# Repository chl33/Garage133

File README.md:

# Garage133

**Garage133** is a DIY garage door automation and monitoring system based on the ESP32 / ESP32-S3.
It provides the capability to remotely control up to two garage doors, monitor their
 state (open/closed), detect vehicle presence using a multi-sonar sensor array,
 measure environmental conditions (temperature/humidity), and detect motion within the garage.

The system integrates seamlessly with **Home Assistant** via MQTT Discovery
 and provides a modern, responsive **Svelte-based Web Interface** for real-time monitoring
 and configuration.

## What's New in v2.1.0

*   **Board v3.1 PCB & Enclosure Updates**: Updated KiCAD design for board v3.1, refined BOM, and enhanced 3D-printed enclosure with labeled connectors, improved USB-C port clearance, and better thermal isolation for the SHTC3 sensor.
*   **Standardized on ESP32-S3 (Board v3.x)**: Retired support and pin definitions for legacy Classic ESP32 (Board v1/v2).
*   **Sonar Watchdog & Stability**: Added sonar ping timeout handling to prevent missed echoes from triggering the ESP32 hardware watchdog.
*   **HMM Visualization & Retraining Tools**: Added an SVG state diagram visualization tool (`analysis/hmm_to_svg.py`) and streamlined characterization workflow in `analysis/retrain.py`.
*   **Published Library Dependencies**: Switched dependency management to published packages (`chl33/og3@^0.7.0`, `chl33/og3x-oled@^0.6.1`, `chl33/og3x-shtc3@^0.6.0`).

## What's New in v2.0.0

*   **Quad-Sonar Array (Dual Sonars per Bay)**: Upgraded from single to dual HC-SR04 ultrasonic sensors per garage door (4 sonars total), providing substantially more robust vehicle detection and door state estimation.
*   **Hardware Board v3.0 (ESP32-S3 Support)**: Added support for the v3.0 PCB powered by the ESP32-S3, featuring updated pin routings, 8MB flash support, and refreshed 3D solder stencil fixtures.
*   **Home Assistant Probability Sensors**: Added real-time HMM state probabilities (`probOpen`, `probCar`, `probEmpty`) to Home Assistant via MQTT Discovery.
*   **Hardened Web UI Build Pipeline**: Pinned `svelteesp32` to v3.2.5 and upgraded GitHub Actions workflows to Node 22 for reliable, deterministic builds.

## Features

*   **Dual Door Control:** Independent control for two garage doors using relays.
*   **Quad-Sonar HMM State Estimation:** Uses **Hidden Markov Models (HMM)** and a 4-sonar sensor array to robustly classify states:
    *   **Open** (Door is rolled up).
    *   **Closed with Car** (Door is down, vehicle present in bay).
    *   **Closed (Empty)** (Door is down, bay is empty).
*   **Modern Web Dashboard:** A responsive Svelte Single Page Application (SPA) to:
    *   Monitor real-time sensor data and door status.
    *   Trigger door relays remotely.
    *   Visualize HMM detection probabilities in real time.
    *   Manually correct and label states to refine detection.
    *   Upload and reload HMM JSON models dynamically.
*   **Environmental Monitoring:** SHTC3 sensor for Temperature and Humidity.
*   **Motion & Light Detection:** PIR sensor for motion and analog light sensor for garage illumination levels.
*   **Home Assistant MQTT Discovery:** Automatic entity discovery for covers, binary sensors, environmental gauges, and state probability metrics.
*   **OLED Display:** Shows live status, IP address, and sensor readings locally.
*   **OTA Updates:** Reliable Over-The-Air firmware updates using expanded flash partitions.

## Hardware

Garage133 is designed for the **Board v3.1 / v3.0 (ESP32-S3)**. Earlier Board v1/v2 (Classic ESP32) revisions have been retired.

### Pinout Configuration

| Component | Board v3.1 / v3.0 (ESP32-S3) | Description |
| :--- | :--- | :--- |
| **Relay (Left)** | GPIO 10 | Left Garage Door Relay Command |
| **Relay (Right)** | GPIO 11 | Right Garage Door Relay Command |
| **Sonar 1 Trig / Echo (Left)** | GPIO 1 / GPIO 5 | Primary Left Ultrasonic Sensor |
| **Sonar 2 Trig / Echo (Left)** | GPIO 3 / GPIO 7 | Secondary Left Ultrasonic Sensor |
| **Sonar 1 Trig / Echo (Right)** | GPIO 2 / GPIO 6 | Primary Right Ultrasonic Sensor |
| **Sonar 2 Trig / Echo (Right)** | GPIO 4 / GPIO 15 | Secondary Right Ultrasonic Sensor |
| **PIR Sensor** | GPIO 12 | PIR Motion Detection |
| **Light Sensor** | GPIO 12 | Analog Light Level |
| **I2C SDA / SCL** | GPIO 8 / GPIO 9 | SHTC3 Sensor & OLED Display |

*Note: Pin definitions are configured in [`src/main.cpp`](file:///home/chris/Projects2/Garage133/src/main.cpp).*

### Fabrication

This repository includes files for fabricating the custom PCB and 3D printed case:
*   **KiCAD:** Circuit board schematics and layouts are located in the `KiCAD/` directory.
*   **3D Parts:** OpenSCAD and STL files for the enclosure, sensor mounts, and solder stencil fixtures are in the `scad/` directory.

Sonar sensor mount design is also [published on Printables](https://www.printables.com/model/1741349-sonar-ball-and-socket-mount).

## Getting Started

### Prerequisites
*   [PlatformIO](https://platformio.org/) (VSCode Extension or CLI)
*   [Node.js & npm](https://nodejs.org/) (Node 22+ recommended for building the Web Interface)
*   Git

### Installation & Build

1.  **Clone the repository:**
    ```bash
    git clone https://github.com/chl33/Garage133.git
    cd Garage133
    ```

2.  **Build the Web Interface:**
    Generate the C++ header containing the compiled Svelte SPA:
    ```bash
    ./build-svelte.sh
    ```

3.  **Configuration:**
    Copy the example configuration files and customize your settings:
    ```bash
    cp secrets.ini.example secrets.ini
    cp local.ini.example local.ini
    ```
    *Note: WiFi and MQTT credentials can also be configured via the captive portal on first boot (when connected to the `garage133` AP) or through the web dashboard settings page.*

4.  **Build and Flash:**
    Connect your board via USB for the initial flash:

    *   **USB Flash (ESP32-S3):**
        ```bash
        pio run -e usb_s3 --target upload
        ```
    *   **OTA Updates (once configured on WiFi):**
        ```bash
        pio run -e wifi_s3 --target upload
        ```

## Usage

### Web Interface
Navigate to the device's IP address in your web browser:
*   **Overview:** Real-time status of both garage doors, ultrasonic distances, and environmental readings.
*   **Door Details:** View live HMM probability charts, manually label states to gather training data, or upload new JSON models.
*   **Settings:** Configure WiFi, MQTT broker, and initiate device restarts.

### Home Assistant Integration
The device automatically publishes Home Assistant MQTT Discovery topics:
*   **Covers:** `left_door`, `right_door` (Open/Close control & state feedback)
*   **Sensors:** `temperature`, `humidity`, `light`, `prob_open`, `prob_car`, `prob_empty`
*   **Binary Sensors:** `car` (vehicle presence per bay), `door`, `motion`

### HMM Analysis Toolkit
The `analysis/` directory contains Python tools to train and evaluate multi-sonar classification models:
*   Download historical telemetry logs from Home Assistant or InfluxDB.
*   Train 4-sonar HMM transition and emission models using the Viterbi algorithm.
*   Evaluate accuracy and export optimized JSON models to upload directly via the web UI.

## Blog Post
For background and detailed design notes on this project, check out the [Garage133 Blog Post](https://selectiveappeal.org/posts/garage133/).

## License
This project is licensed under the MIT License - see the [LICENSE](LICENSE) file for details.

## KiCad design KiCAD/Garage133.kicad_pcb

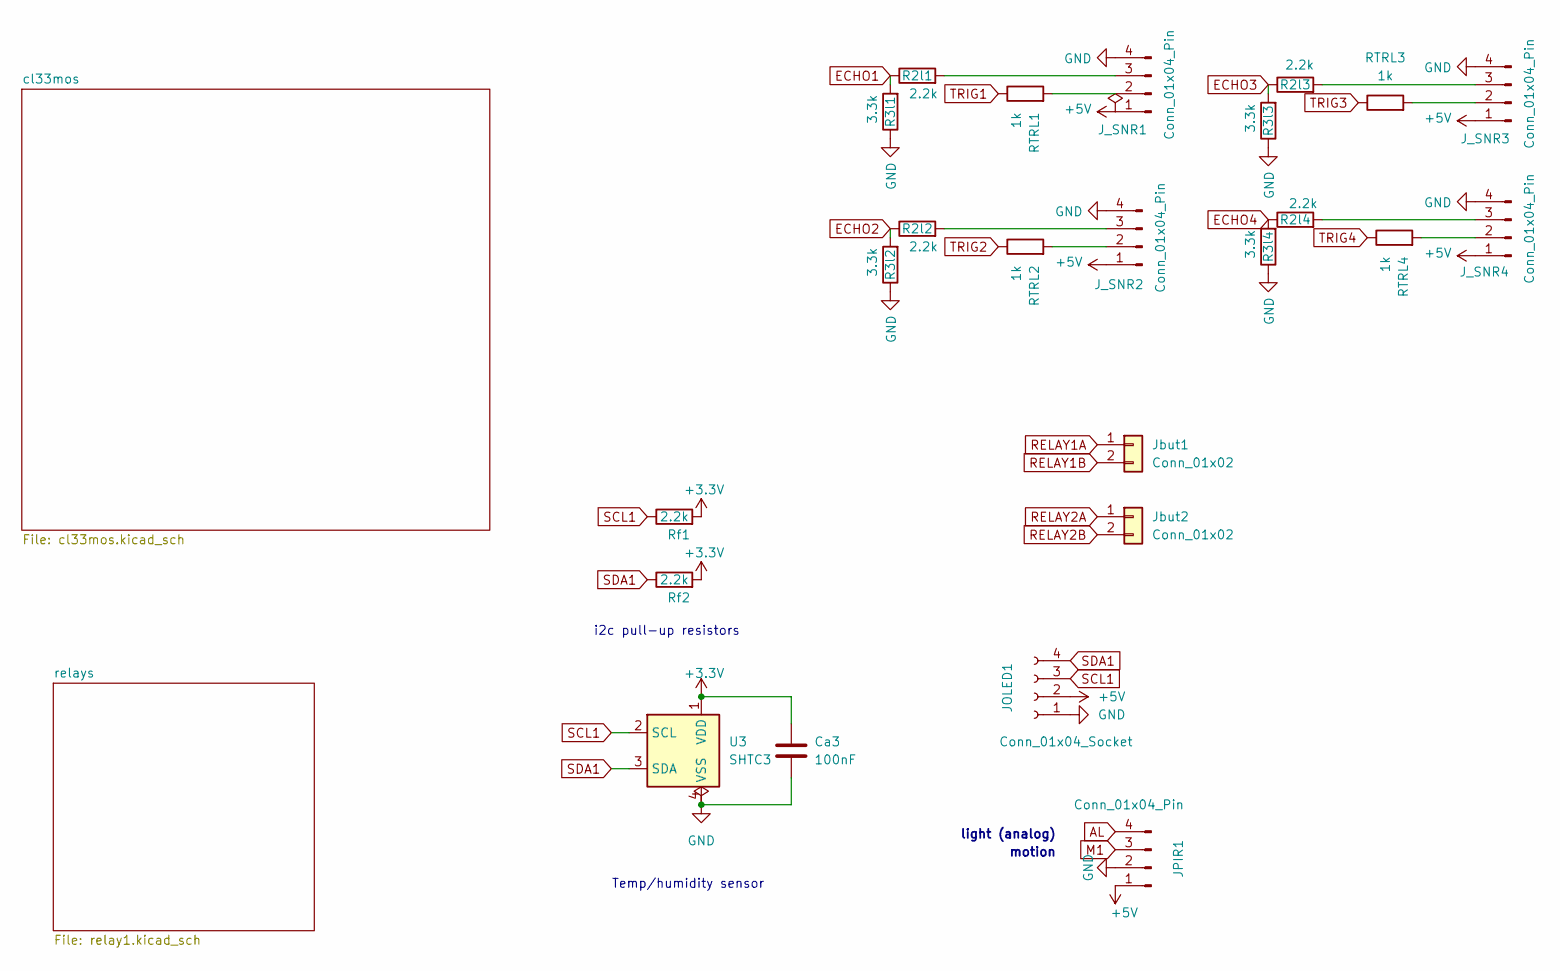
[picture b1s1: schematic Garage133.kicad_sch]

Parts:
Ca3: 100nF; C_0603_1608Metric
JOLED1: Conn_01x04_Socket; PinSocket_1x04_P2.54mm_Vertical
JPIR1: Conn_01x04_Pin; JST_XH_B4B-XH-A_1x04_P2.50mm_Vertical
J_SNR1, J_SNR2, J_SNR3, J_SNR4: Conn_01x04_Pin; JST_XH_B4B-XH-A_1x04_P2.50mm_Vertical
Jbut1, Jbut2: Conn_01x02; JST_XH_B2B-XH-A_1x02_P2.50mm_Vertical
R2l1, R2l2, R2l3, R2l4: 2.2k; R_0603_1608Metric
R3l1, R3l2, R3l3, R3l4: 3.3k; R_0603_1608Metric
RTRL1, RTRL2, RTRL3, RTRL4: 1k; R_0603_1608Metric
Rf1, Rf2: 2.2k; R_0603_1608Metric
U3: SHTC3; Sensirion_DFN-4-1EP_2x2mm_P1mm_EP0.7x1.6mm

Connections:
+3.3V: Ca3.1, Rf1.2, Rf2.2, U3.1 (VDD); also elsewhere on the board
+5V: JOLED1.2, JPIR1.1, J_SNR1.1, J_SNR2.1, J_SNR3.1, J_SNR4.1; also elsewhere on the board
AL: JPIR1.4; also elsewhere on the board
ECHO1: R2l1.1, R3l1.2; also elsewhere on the board
ECHO2: R2l2.1, R3l2.2; also elsewhere on the board
ECHO3: R2l3.1, R3l3.2; also elsewhere on the board
ECHO4: R2l4.1, R3l4.2; also elsewhere on the board
GND: Ca3.2, JOLED1.1, JPIR1.2, J_SNR1.4, J_SNR2.4, J_SNR3.4, J_SNR4.4, R3l1.1, R3l2.1, R3l3.1, R3l4.1, U3.4 (VSS); also elsewhere on the board
M1: JPIR1.3; also elsewhere on the board
unnamed: J_SNR1.2, RTRL1.2
unnamed: J_SNR1.3, R2l1.2
unnamed: J_SNR2.2, RTRL2.2
unnamed: J_SNR2.3, R2l2.2
unnamed: J_SNR3.2, RTRL3.2
unnamed: J_SNR3.3, R2l3.2
unnamed: J_SNR4.2, RTRL4.2
unnamed: J_SNR4.3, R2l4.2
RELAY1A: Jbut1.1; also elsewhere on the board
RELAY1B: Jbut1.2; also elsewhere on the board
RELAY2A: Jbut2.1; also elsewhere on the board
RELAY2B: Jbut2.2; also elsewhere on the board
SCL1: JOLED1.3, Rf1.1, U3.2 (SCL); also elsewhere on the board
SDA1: JOLED1.4, Rf2.1, U3.3 (SDA); also elsewhere on the board
TRIG1: RTRL1.1; also elsewhere on the board
TRIG2: RTRL2.1; also elsewhere on the board
TRIG3: RTRL3.1; also elsewhere on the board
TRIG4: RTRL4.1; also elsewhere on the board

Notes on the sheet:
Temp/humidity sensor
light (analog)
motion
i2c pull-up resistors

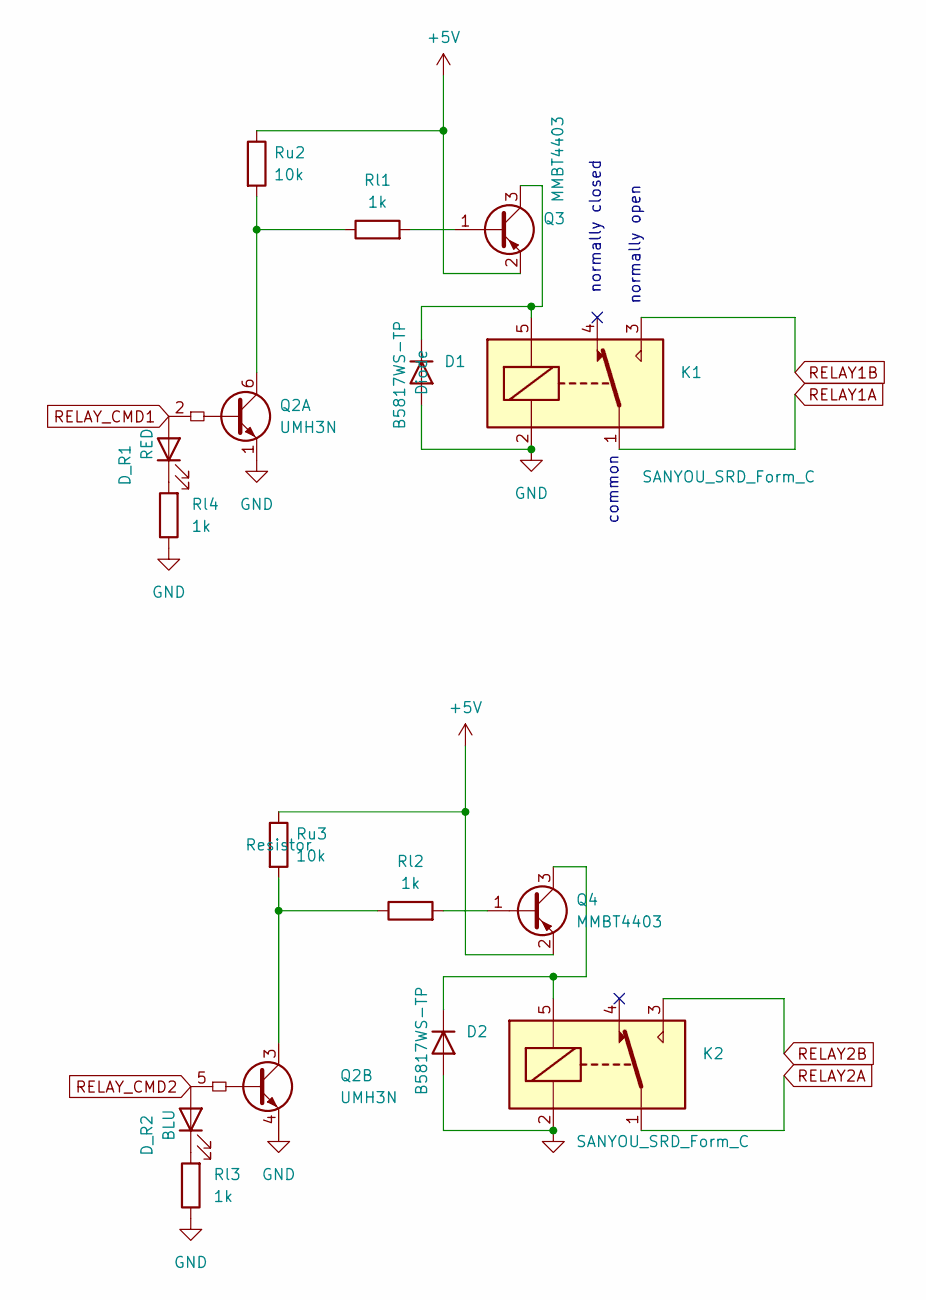
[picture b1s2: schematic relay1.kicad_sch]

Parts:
D1, D2: B5817WS-TP; D_SOD-323
D_R1: RED; LED_0603_1608Metric
D_R2: BLU; LED_0603_1608Metric
K1, K2: SANYOU_SRD_Form_C; Relay_SPDT_SANYOU_SRD_Series_Form_C
Q2: UMH3N; SOT-363_SC-70-6
Q3, Q4: MMBT4403; SOT-23
Rl1, Rl2, Rl3, Rl4: 1k; R_0603_1608Metric
Ru2, Ru3: 10k; R_0603_1608Metric

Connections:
+5V: Q3.2 (E), Q4.2 (E), Ru2.1, Ru3.1; also elsewhere on the board
GND: D1.2 (A), D2.2 (A), K1.2, K2.2, Q2.1 (E1), Q2.4 (E2), Rl3.1, Rl4.1; also elsewhere on the board
unnamed: D1.1 (K), K1.5, Q3.3 (C)
unnamed: D2.1 (K), K2.5, Q4.3 (C)
unnamed: D_R1.1 (K), Rl4.2
unnamed: D_R2.1 (K), Rl3.2
unnamed: Q2.6 (C1), Rl1.1, Ru2.2
unnamed: Q2.3 (C2), Rl2.1, Ru3.2
unnamed: Q3.1 (B), Rl1.2
unnamed: Q4.1 (B), Rl2.2
RELAY1A: K1.1; also elsewhere on the board
RELAY1B: K1.3; also elsewhere on the board
RELAY2A: K2.1; also elsewhere on the board
RELAY2B: K2.3; also elsewhere on the board
RELAY_CMD1: D_R1.2 (A), Q2.2 (B1); also elsewhere on the board
RELAY_CMD2: D_R2.2 (A), Q2.5 (B2); also elsewhere on the board

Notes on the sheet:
normally closed
normally open
common

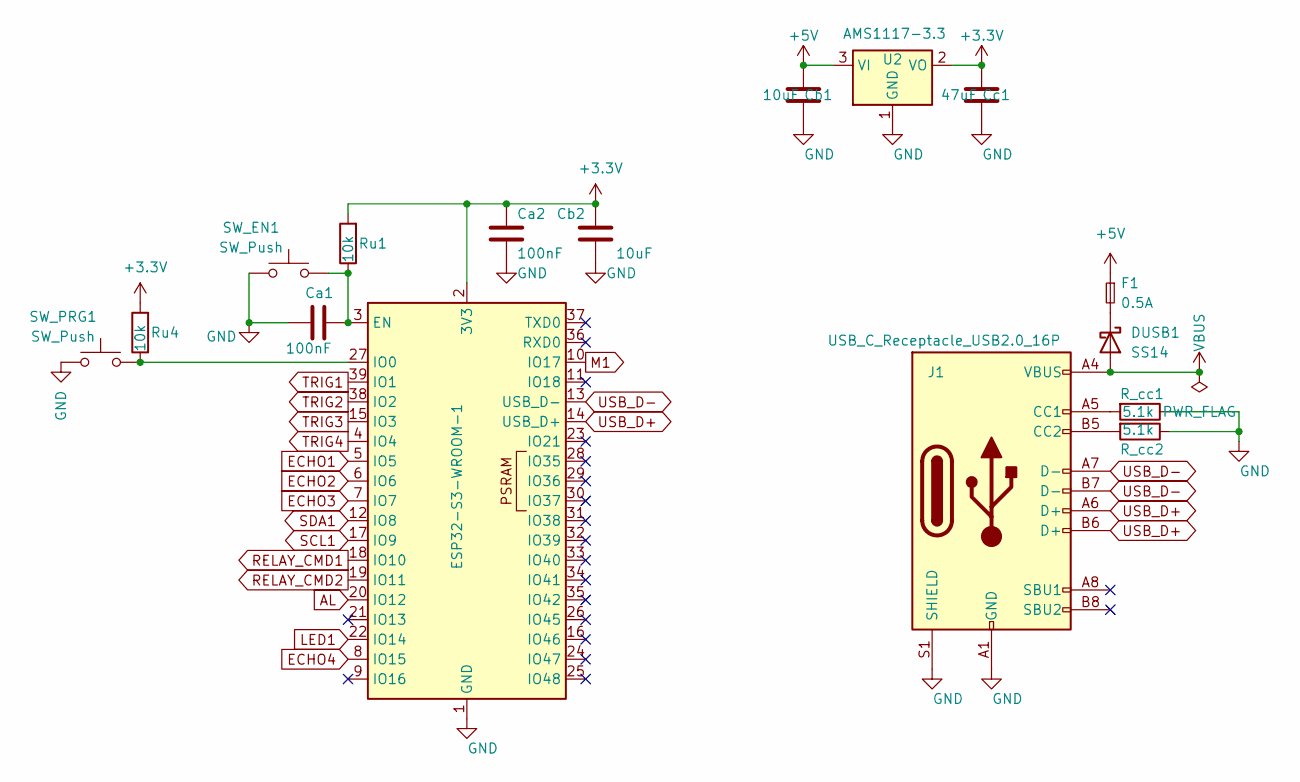
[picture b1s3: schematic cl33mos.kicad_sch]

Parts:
Ca1, Ca2: 100nF; C_0603_1608Metric
Cb1, Cb2: 10uF; C_0805_2012Metric_Pad1.18x1.45mm_HandSolder
Cc1: 47uF; C_0805_2012Metric_Pad1.18x1.45mm_HandSolder
DUSB1: SS14; D_SMA
F1: 0.5A; D_0805_2012Metric
J1: USB_C_Receptacle_USB2.0_16P; USB_C_Receptacle_HRO_TYPE-C-31-M-12
R_cc1, R_cc2: 5.1k; R_0603_1608Metric
Ru1, Ru4: 10k; R_0603_1608Metric
SW_EN1: SW_Push; SW_SPST_FSMSM
SW_PRG1: SW_Push; SW_SPST_FSMSM
U1: ESP32-S3-WROOM-1
U2: AMS1117-3.3; SOT-223-3_TabPin2

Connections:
+3.3V: Ca2.1, Cb2.1, Cc1.1, Ru1.2, Ru4.2, U1.2 (3V3), U2.2 (VO); also elsewhere on the board
+5V: Cb1.1, F1.1, U2.3 (VI); also elsewhere on the board
AL: U1.20 (IO12); also elsewhere on the board
ECHO1: U1.5 (IO5); also elsewhere on the board
ECHO2: U1.6 (IO6); also elsewhere on the board
ECHO3: U1.7 (IO7); also elsewhere on the board
ECHO4: U1.8 (IO15); also elsewhere on the board
GND: Ca1.1, Ca2.2, Cb1.2, Cb2.2, Cc1.2, J1.A1 (GND), J1.A12 (GND), J1.B1 (GND), J1.B12 (GND), J1.S1 (SHIELD), R_cc1.1, R_cc2.1, SW_EN1.1, SW_PRG1.1, U1.1 (GND), U1.40 (GND), U1.41 (GND), U2.1 (GND); also elsewhere on the board
LED1: U1.22 (IO14); also elsewhere on the board
M1: U1.10 (IO17); also elsewhere on the board
unnamed: DUSB1.1 (K), F1.2
unnamed: J1.A5 (CC1), R_cc1.2
unnamed: J1.B5 (CC2), R_cc2.2
unnamed: Ca1.2, Ru1.1, SW_EN1.2, U1.3 (EN)
unnamed: Ru4.1, SW_PRG1.2, U1.27 (IO0)
RELAY_CMD1: U1.18 (IO10); also elsewhere on the board
RELAY_CMD2: U1.19 (IO11); also elsewhere on the board
SCL1: U1.17 (IO9); also elsewhere on the board
SDA1: U1.12 (IO8); also elsewhere on the board
TRIG1: U1.39 (IO1); also elsewhere on the board
TRIG2: U1.38 (IO2); also elsewhere on the board
TRIG3: U1.15 (IO3); also elsewhere on the board
TRIG4: U1.4 (IO4); also elsewhere on the board
USB_D+: J1.A6 (D+), J1.B6 (D+), U1.14 (USB_D+)
USB_D-: J1.A7 (D-), J1.B7 (D-), U1.13 (USB_D-)
VBUS: DUSB1.2 (A), J1.A4 (VBUS), J1.A9 (VBUS), J1.B4 (VBUS), J1.B9 (VBUS)

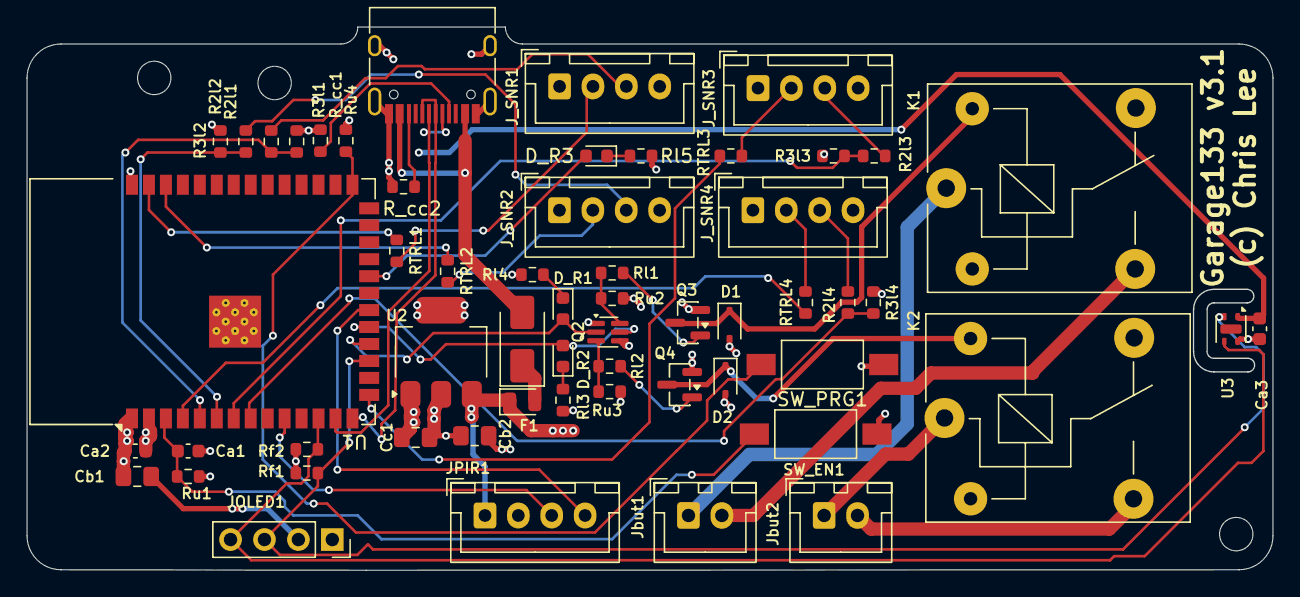
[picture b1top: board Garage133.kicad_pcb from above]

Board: 4 copper layers, 93.2 x 40.6 mm, 57 parts (0 on the bottom side), 47 nets.

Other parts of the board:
D_R3: YLW; LED_0603_1608Metric
Rl5: 1k; R_0603_1608Metric

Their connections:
GND: Rl5.1; also elsewhere on the board
LED1: D_R3.2 (A); also elsewhere on the board
unnamed: D_R3.1 (K), Rl5.2

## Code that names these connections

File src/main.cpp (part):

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// --- Garage133 Hardware Configuration ---

// ESP32-S3 Pin Assignments
const int kRelayLeftPin = 10;   // RELAY_CMD1
const int kRelayRightPin = 11;  // RELAY_CMD2

const int kLeftTrigPin = 1;     // TRIG1
const int kLeftEchoPin = 5;     // ECHO1
const int kRightTrigPin = 2;    // TRIG2
const int kRightEchoPin = 6;    // ECHO2

const int kLeftTrig2Pin = 3;    // TRIG3
const int kLeftEcho2Pin = 7;    // ECHO3
const int kRightTrig2Pin = 4;   // TRIG4
const int kRightEcho2Pin = 15;  // ECHO4

const int kPirPin = 12;         // AL
const int kLightPin = 12;       // AL
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
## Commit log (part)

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2024-09-27 Garage133: initial import
2024-09-27 Garage133: initial import (#1)
2024-09-28 Import EBox and sonar box and mount (OpenSCAD designs).
2024-09-28 KiCAD design for PCB
2024-09-28 Update OpenSCAD model, add KiCAD design (#2)
2024-10-13 README: point to blog post
2024-10-14 readme fix
2024-10-19 update dependencies
2024-10-19 update dependencies (#3)
2024-10-24 update workflows
2024-10-24 add copyright comments
2024-12-31 remove git check in workflow
2024-12-31 og3 version -> 0.2.5
2024-12-31 update workflows (#4)
2025-01-01 Updated readmea and images
2025-01-01 Updated readme and images (#5)
2025-01-01 readme update
2025-01-01 readme update (#6)
2025-08-24 copyright year -> 2025
2025-08-24 upgrade og3 to version 0.3.90
    Make distinct HA devices for left and right doors
2025-10-26 Get variables working again in MQTT/Home Assistant
2025-12-14 Switch to og3 0.4.0, add a watchdog
2025-12-14 fix build
2025-12-14 add uploadHostPort
2025-12-14 update secrets.ini.example for build
2025-12-14 more example secrets fixes
2025-12-14 have platform.ini use secrets-usb.ini for repository
2025-12-14 Update to og3 0.4.0 (#7)
    - Each garage door now is a separate device, with the Garage133 the
    parent device.
    - Added a watchdog, so that if the device gets hung, it reboots in 5
    seconds.
2025-12-20 device_class -> 'garage_door' (was 'garage')
2025-12-20 device_class -> 'garage_door' (was 'garage') (#9)
2025-12-26 device type -> cover, device class -> garage
2025-12-26 device type -> cover, device class -> garage (#10)
2026-01-28 update readme (gemini)
2026-01-28 update readme (gemini) (#11)
2026-02-22 license header update
2026-02-22 tweak logging
2026-02-22 cleanup platformio.ini
2026-02-22 build update (#12)
2026-02-28 Gemini code for training, evaluating, and using HMM models.
    Also, download and organize training data from InfluxDB.
2026-02-28 Initial pass with ruff
2026-02-28 ruff fixes
2026-02-28 fixes to hmm.h
2026-03-01 A bunch of changes from Gemini -- I' not sure they are all correct.
    Especially, the MQTT HA autodiscovery code.
2026-03-01 My edits to try to correct problems with Gemini changes.
2026-03-02 build fix
2026-03-03 fix setting OTA password
2026-03-03 platformio deps: upgrade PsychicHttp
2026-03-03 platformio.ini: usb and wifi uploads are now environments
2026-03-03 Update example .ini files
2026-03-03 Fixed name of temperature, fixed HA discovery for light sensor.
2026-03-09 updated platform.ini organizaiton, added gemini-generated CHANGELOG
2026-03-11 Gemini-generated svelte interface (untested)
2026-03-11 Door configuration pages
2026-03-11 Many tweaks for the Svelte interfcae. Pretty nice now.
2026-03-11 HMM scripts
2026-03-11 Changelog and Readme updates for version 1.0.0.
2026-03-11 remove commented-out obsolete fixes in build-svelte.sh
2026-03-11 remove seom plant133 leftovers
2026-03-11 update platformio for CI build
2026-03-11 CI update for svelte interface build
2026-03-12 Version 1.0.0 (#13)
    - Use og3 0.5.0.
    - HMM classification of garage door state
    - Svelte web interface
2026-03-13 analysis/download: make download script easier to use, linting
2026-03-15 hmm.h: use og3 logger
2026-03-15 hmm updated to use simple matrix class (gemini)
2026-03-15 added python license-header update in utils
2026-03-15 gitignore update
2026-03-15 hmm tweaks
2026-03-15 Added hmm unit test (gemini)
2026-03-15 added copyright, have util/check.sh run unit tests
2026-03-15 Github checks: run ./util/check.sh
2026-03-15 version -> 1.0.1
2026-03-15 fix location of og3 in native compile
2026-03-22 og3 0.6.0: JSON for some core og3 modules now use camelCase
2026-03-22 move zombie web endpoints from plant133
2026-03-22 train-hmm.sh: pass arguments to called code
2026-03-25 gemini fixes for new dependency system
2026-03-27 Use published versions of libraries, delay between sonar readings
2026-03-27 use published og3 for native build
2026-03-27 Update README and CHANGELOG.
2026-03-27 missing image
2026-03-27 enlarge image
2026-03-27 version 1.0.3: Infrastructure updates, og3 0.6.0 (#14)
2026-04-03 Add dependabot, update JSON for wifi/mqtt pages
2026-04-03 bumped deps & software version
2026-04-03 version 1.0.4 (#15)
2026-04-03 Bump actions/setup-node from 4 to 6
    Bumps [actions/setup-node](https://github.com/actions/setup-node) from 4 to 6.
    - [Release notes](https://github.com/actions/setup-node/releases)
    - [Commits](https://github.com/actions/setup-node/compare/v4...v6)
    ---
    updated-dependencies:
    - dependency-name: actions/setup-node
2026-04-03 Bump actions/setup-python from 5 to 6
    Bumps [actions/setup-python](https://github.com/actions/setup-python) from 5 to 6.
    - [Release notes](https://github.com/actions/setup-python/releases)
    - [Commits](https://github.com/actions/setup-python/compare/v5...v6)
    ---
    updated-dependencies:
    - dependency-name: actions/setup-python
2026-04-03 Bump actions/checkout from 4 to 6
    Bumps [actions/checkout](https://github.com/actions/checkout) from 4 to 6.
    - [Release notes](https://github.com/actions/checkout/releases)
    - [Changelog](https://github.com/actions/checkout/blob/main/CHANGELOG.md)
    - [Commits](https://github.com/actions/checkout/compare/v4...v6)
    ---
    updated-dependencies:
2026-04-03 Bump actions/checkout from 4 to 6 (#19)
    Bumps [actions/checkout](https://github.com/actions/checkout) from 4 to
    6.
    <details>
    <summary>Release notes</summary>
    <p><em>Sourced from <a
    href="https://github.com/actions/checkout/releases">actions/checkout's
2026-04-03 Bump actions/setup-python from 5 to 6 (#18)
    Bumps [actions/setup-python](https://github.com/actions/setup-python)
    from 5 to 6.
    <details>
    <summary>Release notes</summary>
    <p><em>Sourced from <a
    href="https://github.com/actions/setup-python/releases">actions/setup-python's
2026-04-03 Bump actions/cache from 4 to 5
    Bumps [actions/cache](https://github.com/actions/cache) from 4 to 5.
    - [Release notes](https://github.com/actions/cache/releases)
    - [Changelog](https://github.com/actions/cache/blob/main/RELEASES.md)
    - [Commits](https://github.com/actions/cache/compare/v4...v5)
    ---
    updated-dependencies:
2026-04-03 Bump actions/setup-node from 4 to 6 (#16)
    Bumps [actions/setup-node](https://github.com/actions/setup-node) from 4
    to 6.
    <details>
    <summary>Release notes</summary>
    <p><em>Sourced from <a
    href="https://github.com/actions/setup-node/releases">actions/setup-node's
2026-04-03 Bump actions/cache from 4 to 5 (#17)
    Bumps [actions/cache](https://github.com/actions/cache) from 4 to 5.
    <details>
    <summary>Release notes</summary>
    <p><em>Sourced from <a
    href="https://github.com/actions/cache/releases">actions/cache's
    releases</a>.</em></p>
2026-04-11 Publish state probabilities to Home Assistant via MQTT.
2026-04-11 WifiConfig: restart board if config changes
2026-04-11 version -> 1.0.5
2026-04-12 v1.0.5 (#20)
    Add garage state probabilities to HA-exported variables.
2026-06-19 Bump actions/checkout from 6 to 7
    Bumps [actions/checkout](https://github.com/actions/checkout) from 6 to 7.
    - [Release notes](https://github.com/actions/checkout/releases)
    - [Changelog](https://github.com/actions/checkout/blob/main/CHANGELOG.md)
    - [Commits](https://github.com/actions/checkout/compare/v6...v7)
    ---
    updated-dependencies:
2026-06-19 Bump actions/checkout from 6 to 7 (#21)
    Bumps [actions/checkout](https://github.com/actions/checkout) from 6 to
    7.
    <details>
    <summary>Release notes</summary>
    <p><em>Sourced from <a
    href="https://github.com/actions/checkout/releases">actions/checkout's
2026-06-24 Bump actions/cache from 5 to 6
    Bumps [actions/cache](https://github.com/actions/cache) from 5 to 6.
    - [Release notes](https://github.com/actions/cache/releases)
    - [Changelog](https://github.com/actions/cache/blob/main/RELEASES.md)
    - [Commits](https://github.com/actions/cache/compare/v5...v6)
    ---
    updated-dependencies:

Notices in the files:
src/main.cpp:
Copyright (c) 2026 Chris Lee and contributors.
Licensed under the MIT license. See LICENSE file in the project root for details.
